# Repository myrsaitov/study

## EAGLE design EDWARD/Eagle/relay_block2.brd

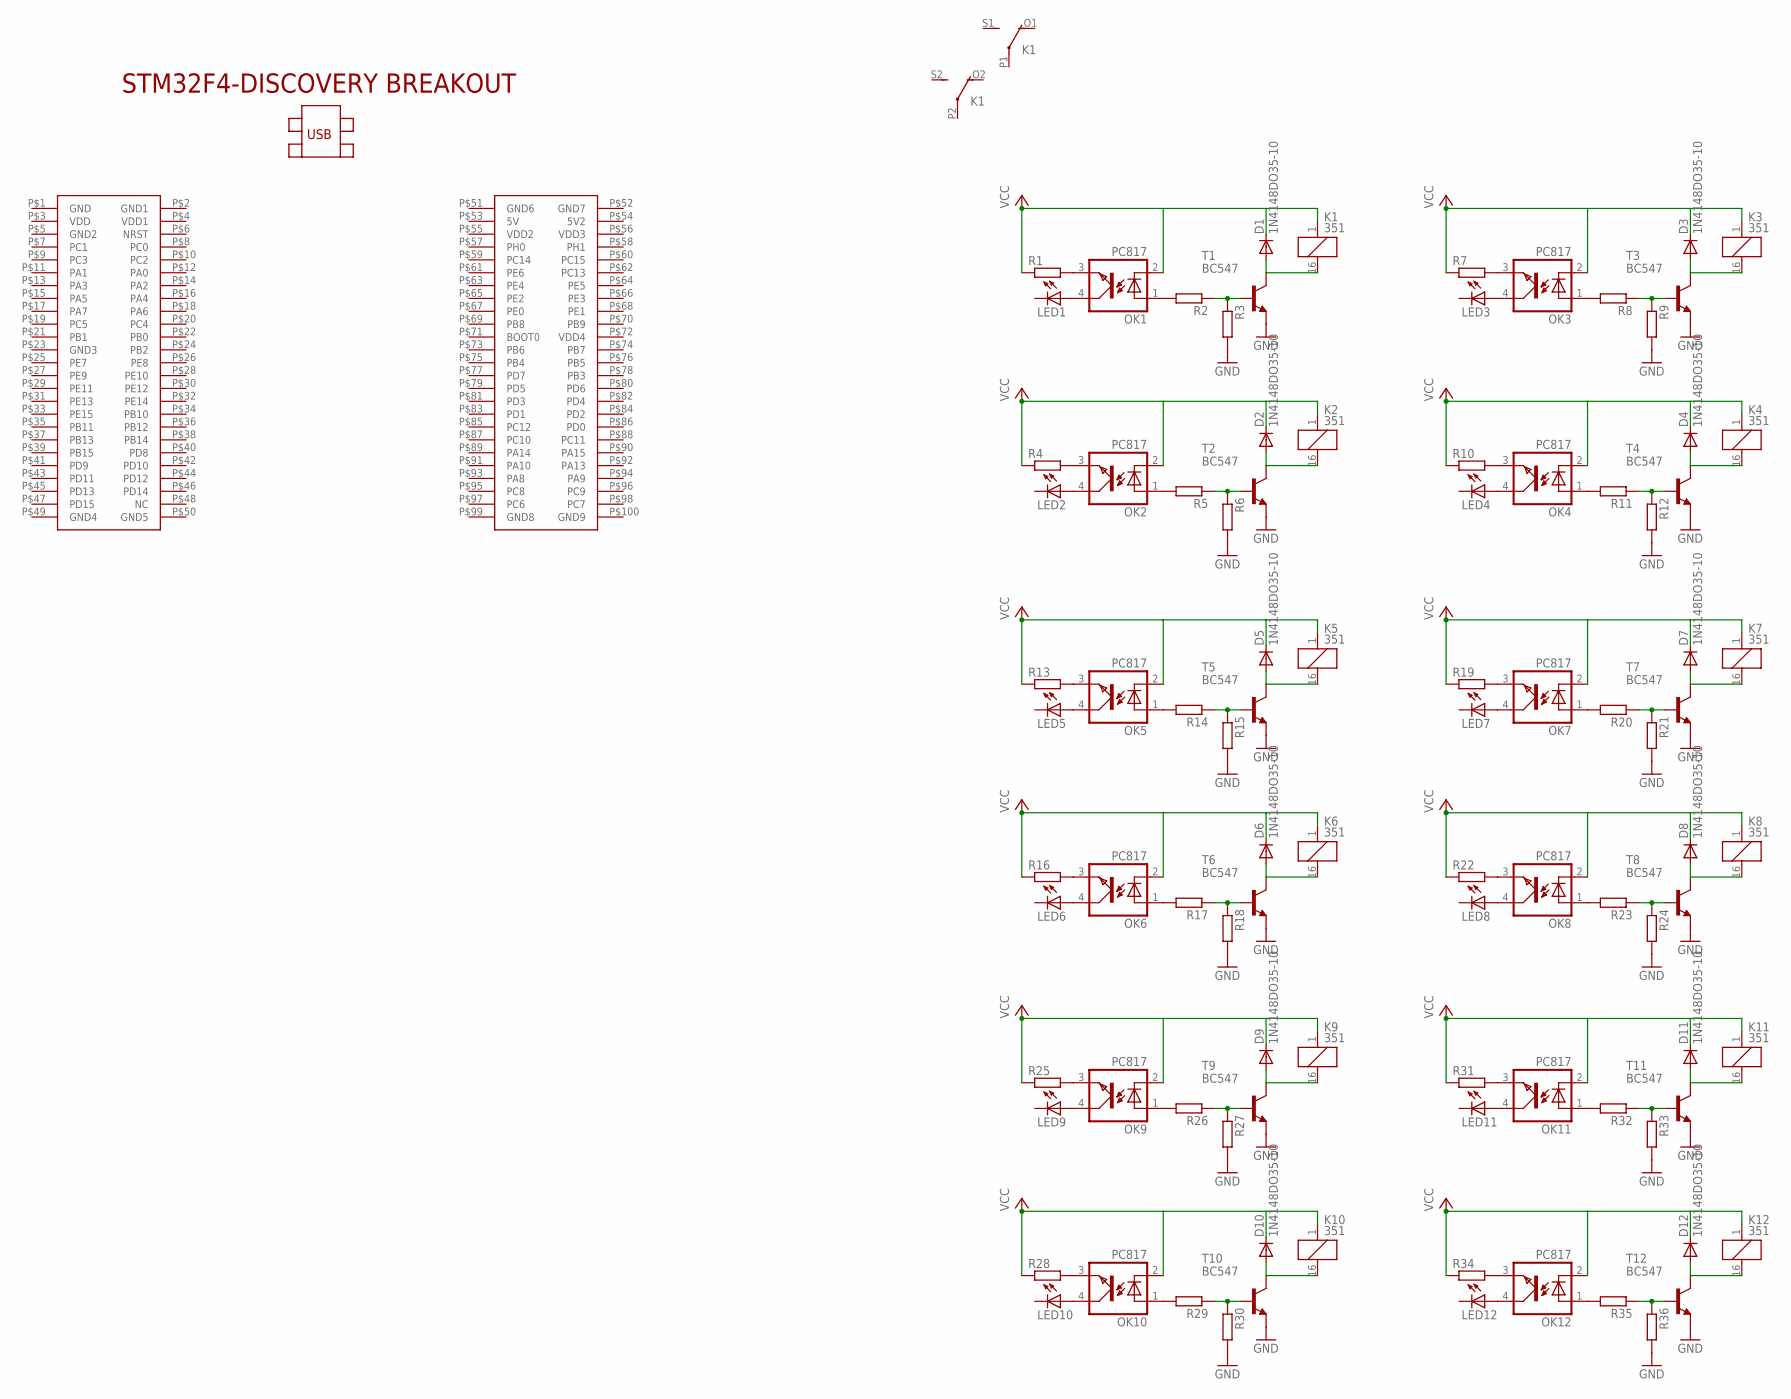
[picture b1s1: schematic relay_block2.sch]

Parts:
D1, D2, D3, D4, D5, D6, D7, D8, D9, D10, D11, D12: 1N4148DO35-10; DO35-10
K1, K2, K3, K4, K5, K6, K7, K8, K9, K10, K11, K12: 351
LED1, LED2, LED3, LED4, LED5, LED6, LED7, LED8, LED9, LED10, LED11, LED12: LED_ELD260; LED_LD260
OK1, OK2, OK3, OK4, OK5, OK6, OK7, OK8, OK9, OK10, OK11, OK12: PC817; DIL04
R1, R2, R3, R4, R5, R6, R7, R8, R9, R10, R11, R12, R13, R14, R15, R16, R17, R18, R19, R20, R21, R22, R23, R24, R25, R26, R27, R28, R29, R30, R31, R32, R33, R34, R35, R36: R-EU_M1206; M1206
T1, T2, T3, T4, T5, T6, T7, T8, T9, T10, T11, T12: BC547; TO92
U$1: STM32F4-DISCOVERY_STM32F4-DISCOVERY

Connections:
GND: R3.2, R6.2, R9.2, R12.2, R15.2, R18.2, R21.2, R24.2, R27.2, R30.2, R33.2, R36.2, T1.1 (E), T2.1 (E), T3.1 (E), T4.1 (E), T5.1 (E), T6.1 (E), T7.1 (E), T8.1 (E), T9.1 (E), T10.1 (E), T11.1 (E), T12.1 (E)
unnamed: OK1.3 (EMIT), R1.2
unnamed: LED1.A, OK1.4 (COL)
unnamed: OK1.1 (A), R2.2
unnamed: R2.1, R3.1, T1.2 (B)
unnamed: D1.A, K1.16 (2), T1.3 (C)
unnamed: OK2.3 (EMIT), R4.2
unnamed: LED2.A, OK2.4 (COL)
unnamed: OK2.1 (A), R5.2
unnamed: R5.1, R6.1, T2.2 (B)
unnamed: D2.A, K2.16 (2), T2.3 (C)
unnamed: OK3.3 (EMIT), R7.2
unnamed: LED3.A, OK3.4 (COL)
unnamed: OK3.1 (A), R8.2
unnamed: R8.1, R9.1, T3.2 (B)
unnamed: D3.A, K3.16 (2), T3.3 (C)
unnamed: OK4.3 (EMIT), R10.2
unnamed: LED4.A, OK4.4 (COL)
unnamed: OK4.1 (A), R11.2
unnamed: R11.1, R12.1, T4.2 (B)
unnamed: D4.A, K4.16 (2), T4.3 (C)
unnamed: OK5.3 (EMIT), R13.2
unnamed: LED5.A, OK5.4 (COL)
unnamed: OK5.1 (A), R14.2
unnamed: R14.1, R15.1, T5.2 (B)
unnamed: D5.A, K5.16 (2), T5.3 (C)
unnamed: OK6.3 (EMIT), R16.2
unnamed: LED6.A, OK6.4 (COL)
unnamed: OK6.1 (A), R17.2
unnamed: R17.1, R18.1, T6.2 (B)
unnamed: D6.A, K6.16 (2), T6.3 (C)
unnamed: OK7.3 (EMIT), R19.2
unnamed: LED7.A, OK7.4 (COL)
unnamed: OK7.1 (A), R20.2
unnamed: R20.1, R21.1, T7.2 (B)
unnamed: D7.A, K7.16 (2), T7.3 (C)
unnamed: OK8.3 (EMIT), R22.2
unnamed: LED8.A, OK8.4 (COL)
unnamed: OK8.1 (A), R23.2
unnamed: R23.1, R24.1, T8.2 (B)
unnamed: D8.A, K8.16 (2), T8.3 (C)
unnamed: OK9.3 (EMIT), R25.2
unnamed: LED9.A, OK9.4 (COL)
unnamed: OK9.1 (A), R26.2
unnamed: R26.1, R27.1, T9.2 (B)
unnamed: D9.A, K9.16 (2), T9.3 (C)
unnamed: OK10.3 (EMIT), R28.2
unnamed: LED10.A, OK10.4 (COL)
unnamed: OK10.1 (A), R29.2
unnamed: R29.1, R30.1, T10.2 (B)
unnamed: D10.A, K10.16 (2), T10.3 (C)
unnamed: OK11.3 (EMIT), R31.2
unnamed: LED11.A, OK11.4 (COL)
unnamed: OK11.1 (A), R32.2
unnamed: R32.1, R33.1, T11.2 (B)
unnamed: D11.A, K11.16 (2), T11.3 (C)
unnamed: OK12.3 (EMIT), R34.2
unnamed: LED12.A, OK12.4 (COL)
unnamed: OK12.1 (A), R35.2
unnamed: R35.1, R36.1, T12.2 (B)
unnamed: D12.A, K12.16 (2), T12.3 (C)
VCC: D1.C, D2.C, D3.C, D4.C, D5.C, D6.C, D7.C, D8.C, D9.C, D10.C, D11.C, D12.C, K1.1, K2.1, K3.1, K4.1, K5.1, K6.1, K7.1, K8.1, K9.1, K10.1, K11.1, K12.1, OK1.2 (C), OK2.2 (C), OK3.2 (C), OK4.2 (C), OK5.2 (C), OK6.2 (C), OK7.2 (C), OK8.2 (C), OK9.2 (C), OK10.2 (C), OK11.2 (C), OK12.2 (C), R1.1, R4.1, R7.1, R10.1, R13.1, R16.1, R19.1, R22.1, R25.1, R28.1, R31.1, R34.1

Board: 2 copper layers, 97 parts (0 on the bottom side), 62 nets, no tracks yet.

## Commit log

2017-04-06 second
